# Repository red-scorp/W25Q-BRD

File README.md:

# W25Q-BRD project

W25Q-BRD project is meant to provide people with cheap SPI flash breakout board.

## W25Q-BRD

**W25Q-BRD** is a breakout board for DIY use.
This board features 128Mbit (16MB) serial flash chip W25Q128JVSIQ and M3 mounting hole.
The flash board runs on 3.3V and supports SPI and QSPI transfer modes.

Preview:

[Schematics in PDF format](doc/W25Q-BRD.pdf)

Features:

- Uses 3.3V voltage
- Runs in SPI and QSPI modes
- Simple 2 layer board design
- Common for DIY 2.54mm pitch connector
- Features SIOC-8 and WSON-8(6x5) footprints

CAM files are available.
JLCPCB BOM and CPL files are available.

### W25Q-BRD v1.0

Preview:

Initial version of the board.

### W25Q-BRD v1.1

Preview:

Added capacitors for better voltage stability.

### W25Q-BRD v1.2

Preview:

Added alternative WSON footprint to add more fabrication options.

## Board pinout

<table>
    <thead>
        <tr>
            <th>Pin</th><th>SPI mode</th><th>QSPI mode</th>
        </tr>
    </thead>
    <tbody>
        <tr>
            <td>3V3</td><td colspan=2>VCC of the chip, 3.3V</td>
        </tr>
        <tr>
            <td>NCS</td><td colspan=2>Chip select signal</td>
        </tr>
        <tr>
            <td>IO0</td><td>Data input</td><td>Data IO 0</td>
        </tr>
        <tr>
            <td>IO1</td><td>Data output</td><td>Data IO 1</td>
        </tr>
        <tr>
            <td>IO2</td><td>-</td><td>Data IO 2</td>
        </tr>
        <tr>
            <td>IO3</td><td>-</td><td>Data IO 3</td>
        </tr>
        <tr>
            <td>CLK</td><td colspan=2>(Q)SPI clock signal</td>
        </tr>
        <tr>
            <td>GND</td><td colspan=2>Ground</td>
        </tr>
    </tbody>
</table>

## Links

- Flash chip [W25Q128JVSIQ datasheet](doc/1811142111_Winbond-Elec-W25Q128JVSIQ_C97521.pdf)

## How to help

Your contributions as code, resources, or finances are welcome! Please contact me directly via email at andriy.golovnya@gmail.com or through my [GitHub profile](https://github.com/red-scorp).

If you'd like to make a financial contribution, you can donate via [PayPal](http://paypal.me/redscorp) or [Ko-Fi](http://ko-fi.com/redscorp). Your support is greatly appreciated.

Thanks in advance!

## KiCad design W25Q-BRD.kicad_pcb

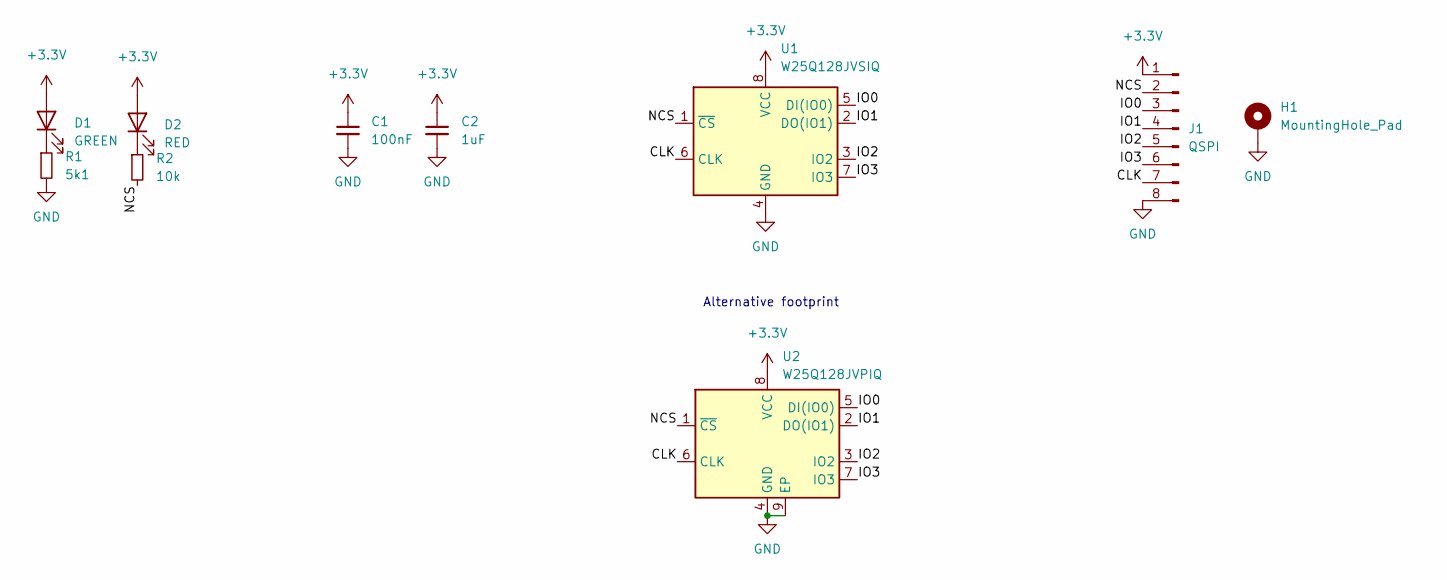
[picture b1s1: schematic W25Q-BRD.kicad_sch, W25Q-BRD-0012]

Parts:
C1: 100nF; C_0402_1005Metric
C2: 1uF; C_0603_1608Metric
D1: GREEN; LED_0603_1608Metric
D2: RED; LED_0603_1608Metric
H1: MountingHole_Pad; MountingHole_3.2mm_M3_Pad_Via
J1: QSPI; PinHeader_1x08_P2.54mm_Vertical
R1: 5k1; R_0402_1005Metric
R2: 10k; R_0402_1005Metric
U1: W25Q128JVSIQ; SOIC-8_5.23x5.23mm_P1.27mm
U2: W25Q128JVPIQ; WSON-8-1EP_6x5mm_P1.27mm_EP3.4x4.3mm

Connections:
+3.3V: C1.1, C2.1, D1.2 (A), D2.2 (A), J1.1, U1.8 (VCC), U2.8 (VCC)
/CLK: J1.7, U1.6 (CLK), U2.6 (CLK)
/IO0: J1.3, U1.5 (DI(IO0)), U2.5 (DI(IO0))
/IO1: J1.4, U1.2 (DO(IO1)), U2.2 (DO(IO1))
/IO2: J1.5, U1.3 (IO2), U2.3 (IO2)
/IO3: J1.6, U1.7 (IO3), U2.7 (IO3)
/NCS: J1.2, R2.2, U1.1 (~CS), U2.1 (~CS)
GND: C1.2, C2.2, H1.1, J1.8, R1.2, U1.4 (GND), U2.4 (GND), U2.9 (EP)
unnamed: D1.1 (K), R1.1
unnamed: D2.1 (K), R2.1

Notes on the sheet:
Alternative footprint

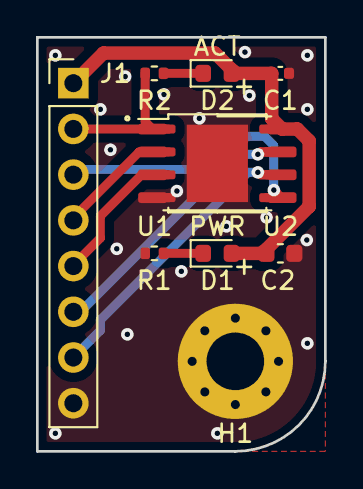
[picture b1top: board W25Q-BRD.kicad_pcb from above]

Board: 2 copper layers, 16.0 x 23.0 mm, 10 parts (0 on the bottom side), 10 nets.

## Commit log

2022-12-04 New board project created.
2022-12-04 Finished board design.
2022-12-04 Added CAM files
2022-12-04 Moved some components around. Generated CAM files.
2022-12-04 Generated BoM and CPL files.
2022-12-04 Fixed BoM and CPL files during ordering.
2022-12-05 Version 1.1. Added 2 caps. Added few texts.
2022-12-05 Generated CAM, BoM and CPL files.
2022-12-09 Fixed .gitignore to be generic one.
2022-12-09 Added fitting 3D mode for the flash chip.
2022-12-09 Generated PDF schematics.
2022-12-09 Generated PNG previews.
2022-12-09 Added W25Q128JVSIQ datasheet.
2022-12-09 Added README.md file.
2022-12-09 Added pinout table. Fixed few typos.
2022-12-27 Added alternative footprint for WSOT-8 version of the chip.
2022-12-29 Added v1.2 to README.
2022-12-31 Added side-by-side images for board previews.
2023-07-12 Added FUNDING.yml
